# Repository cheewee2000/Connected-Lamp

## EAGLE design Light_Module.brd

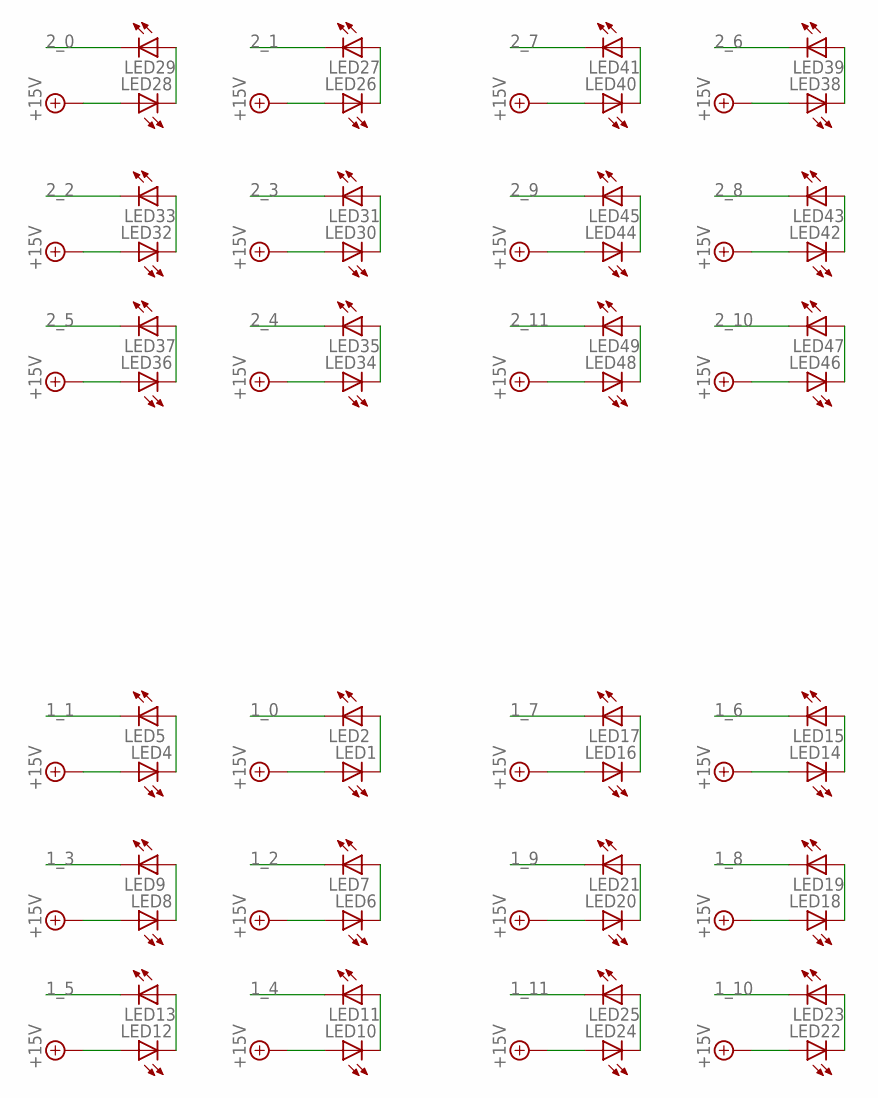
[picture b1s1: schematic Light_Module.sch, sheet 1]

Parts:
LED1, LED2, LED4, LED5, LED6, LED7, LED8, LED9, LED10, LED11, LED12, LED13, LED14, LED15, LED16, LED17, LED18, LED19, LED20, LED21, LED22, LED23, LED24, LED25, LED26, LED27, LED28, LED29, LED30, LED31, LED32, LED33, LED34, LED35, LED36, LED37, LED38, LED39, LED40, LED41, LED42, LED43, LED44, LED45, LED46, LED47, LED48, LED49: LED; DS205

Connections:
1_0: LED2.P$2 (C); also elsewhere on the board
1_1: LED5.P$2 (C); also elsewhere on the board
1_2: LED7.P$2 (C); also elsewhere on the board
1_3: LED9.P$2 (C); also elsewhere on the board
1_4: LED11.P$2 (C); also elsewhere on the board
1_5: LED13.P$2 (C); also elsewhere on the board
1_6: LED15.P$2 (C); also elsewhere on the board
1_7: LED17.P$2 (C); also elsewhere on the board
1_8: LED19.P$2 (C); also elsewhere on the board
1_9: LED21.P$2 (C); also elsewhere on the board
1_10: LED23.P$2 (C); also elsewhere on the board
1_11: LED25.P$2 (C); also elsewhere on the board
2_0: LED29.P$2 (C); also elsewhere on the board
2_1: LED27.P$2 (C); also elsewhere on the board
2_2: LED33.P$2 (C); also elsewhere on the board
2_3: LED31.P$2 (C); also elsewhere on the board
2_4: LED35.P$2 (C); also elsewhere on the board
2_5: LED37.P$2 (C); also elsewhere on the board
2_6: LED39.P$2 (C); also elsewhere on the board
2_7: LED41.P$2 (C); also elsewhere on the board
2_8: LED43.P$2 (C); also elsewhere on the board
2_9: LED45.P$2 (C); also elsewhere on the board
2_10: LED47.P$2 (C); also elsewhere on the board
2_11: LED49.P$2 (C); also elsewhere on the board
+15V: LED1.P$1 (A), LED4.P$1 (A), LED6.P$1 (A), LED8.P$1 (A), LED10.P$1 (A), LED12.P$1 (A), LED14.P$1 (A), LED16.P$1 (A), LED18.P$1 (A), LED20.P$1 (A), LED22.P$1 (A), LED24.P$1 (A), LED26.P$1 (A), LED28.P$1 (A), LED30.P$1 (A), LED32.P$1 (A), LED34.P$1 (A), LED36.P$1 (A), LED38.P$1 (A), LED40.P$1 (A), LED42.P$1 (A), LED44.P$1 (A), LED46.P$1 (A), LED48.P$1 (A); also elsewhere on the board
unnamed: LED1.P$2 (C), LED2.P$1 (A)
unnamed: LED4.P$2 (C), LED5.P$1 (A)
unnamed: LED6.P$2 (C), LED7.P$1 (A)
unnamed: LED8.P$2 (C), LED9.P$1 (A)
unnamed: LED10.P$2 (C), LED11.P$1 (A)
unnamed: LED12.P$2 (C), LED13.P$1 (A)
unnamed: LED14.P$2 (C), LED15.P$1 (A)
unnamed: LED16.P$2 (C), LED17.P$1 (A)
unnamed: LED18.P$2 (C), LED19.P$1 (A)
unnamed: LED20.P$2 (C), LED21.P$1 (A)
unnamed: LED22.P$2 (C), LED23.P$1 (A)
unnamed: LED24.P$2 (C), LED25.P$1 (A)
unnamed: LED26.P$2 (C), LED27.P$1 (A)
unnamed: LED28.P$2 (C), LED29.P$1 (A)
unnamed: LED30.P$2 (C), LED31.P$1 (A)
unnamed: LED32.P$2 (C), LED33.P$1 (A)
unnamed: LED34.P$2 (C), LED35.P$1 (A)
unnamed: LED36.P$2 (C), LED37.P$1 (A)
unnamed: LED38.P$2 (C), LED39.P$1 (A)
unnamed: LED40.P$2 (C), LED41.P$1 (A)
unnamed: LED42.P$2 (C), LED43.P$1 (A)
unnamed: LED44.P$2 (C), LED45.P$1 (A)
unnamed: LED46.P$2 (C), LED47.P$1 (A)
unnamed: LED48.P$2 (C), LED49.P$1 (A)

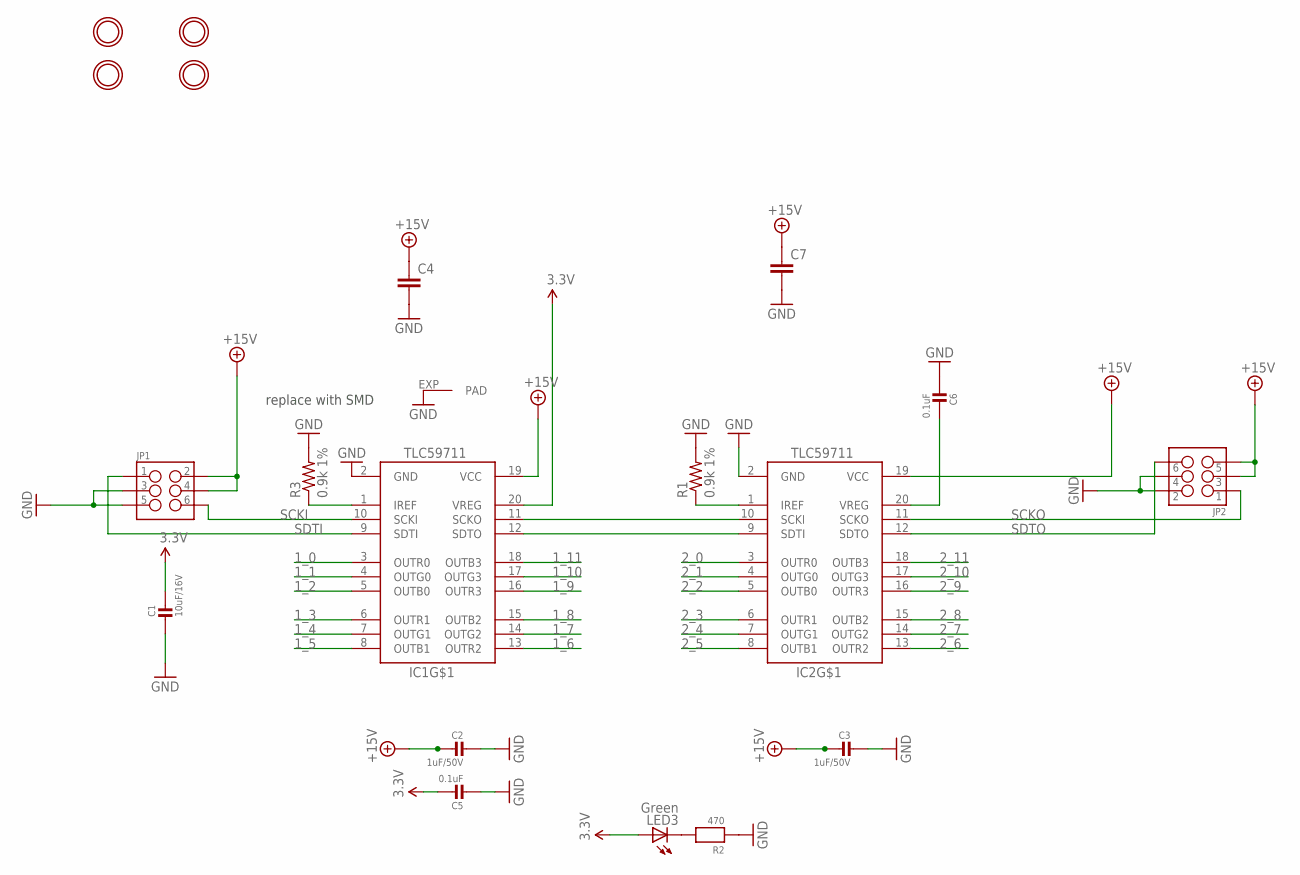
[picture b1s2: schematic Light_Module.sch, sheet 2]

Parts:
C1: 10uF/16V; 0805
C2, C3: 1uF/50V; 0805
C4: CAP1206; 1206
C5, C6: 0.1uF; 0805
C7: CAP_; AXIAL-5MM
IC1, IC2: TLC59711; HTSSOP20DAP
JP1, JP2: M03X2FEMALE_SMD; 2X3_SMD
LED3: Green; CHIP-LED0805
R1, R3: 0.9k 1%; 1206
R2: 470; 0805
U$1, U$2, U$3, U$4: MOUNTINGHOLE2.5; MOUNTINGHOLE_2.5_PLATED

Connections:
1_0: IC1.3 (OUTR0); also elsewhere on the board
1_1: IC1.4 (OUTG0); also elsewhere on the board
1_2: IC1.5 (OUTB0); also elsewhere on the board
1_3: IC1.6 (OUTR1); also elsewhere on the board
1_4: IC1.7 (OUTG1); also elsewhere on the board
1_5: IC1.8 (OUTB1); also elsewhere on the board
1_6: IC1.13 (OUTR2); also elsewhere on the board
1_7: IC1.14 (OUTG2); also elsewhere on the board
1_8: IC1.15 (OUTB2); also elsewhere on the board
1_9: IC1.16 (OUTR3); also elsewhere on the board
1_10: IC1.17 (OUTG3); also elsewhere on the board
1_11: IC1.18 (OUTB3); also elsewhere on the board
2_0: IC2.3 (OUTR0); also elsewhere on the board
2_1: IC2.4 (OUTG0); also elsewhere on the board
2_2: IC2.5 (OUTB0); also elsewhere on the board
2_3: IC2.6 (OUTR1); also elsewhere on the board
2_4: IC2.7 (OUTG1); also elsewhere on the board
2_5: IC2.8 (OUTB1); also elsewhere on the board
2_6: IC2.13 (OUTR2); also elsewhere on the board
2_7: IC2.14 (OUTG2); also elsewhere on the board
2_8: IC2.15 (OUTB2); also elsewhere on the board
2_9: IC2.16 (OUTR3); also elsewhere on the board
2_10: IC2.17 (OUTG3); also elsewhere on the board
2_11: IC2.18 (OUTB3); also elsewhere on the board
3.3V: C1.1, C5.1, IC1.20 (VREG), LED3.A
+15V: C2.1, C3.1, C4.1, C7.P$1 (1), IC1.19 (VCC), IC2.19 (VCC), JP1.2, JP1.4, JP2.3, JP2.5; also elsewhere on the board
GND: C1.2, C2.2, C3.2, C4.2, C5.2, C6.2, C7.P$2 (2), IC1.2 (GND), IC1.EXP (PAD), IC2.2 (GND), JP1.3, JP1.5, JP2.2, JP2.4, R1.2, R2.1, R3.2
unnamed: LED3.C, R2.2
unnamed: IC1.1 (IREF), R3.1
unnamed: IC2.1 (IREF), R1.1
unnamed: IC1.11 (SCKO), IC2.10 (SCKI)
unnamed: IC1.12 (SDTO), IC2.9 (SDTI)
unnamed: C6.1, IC2.20 (VREG)
SCKI: IC1.10 (SCKI), JP1.6
SCKO: IC2.11 (SCKO), JP2.1
SDTI: IC1.9 (SDTI), JP1.1
SDTO: IC2.12 (SDTO), JP2.6

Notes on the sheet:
replace with SMD

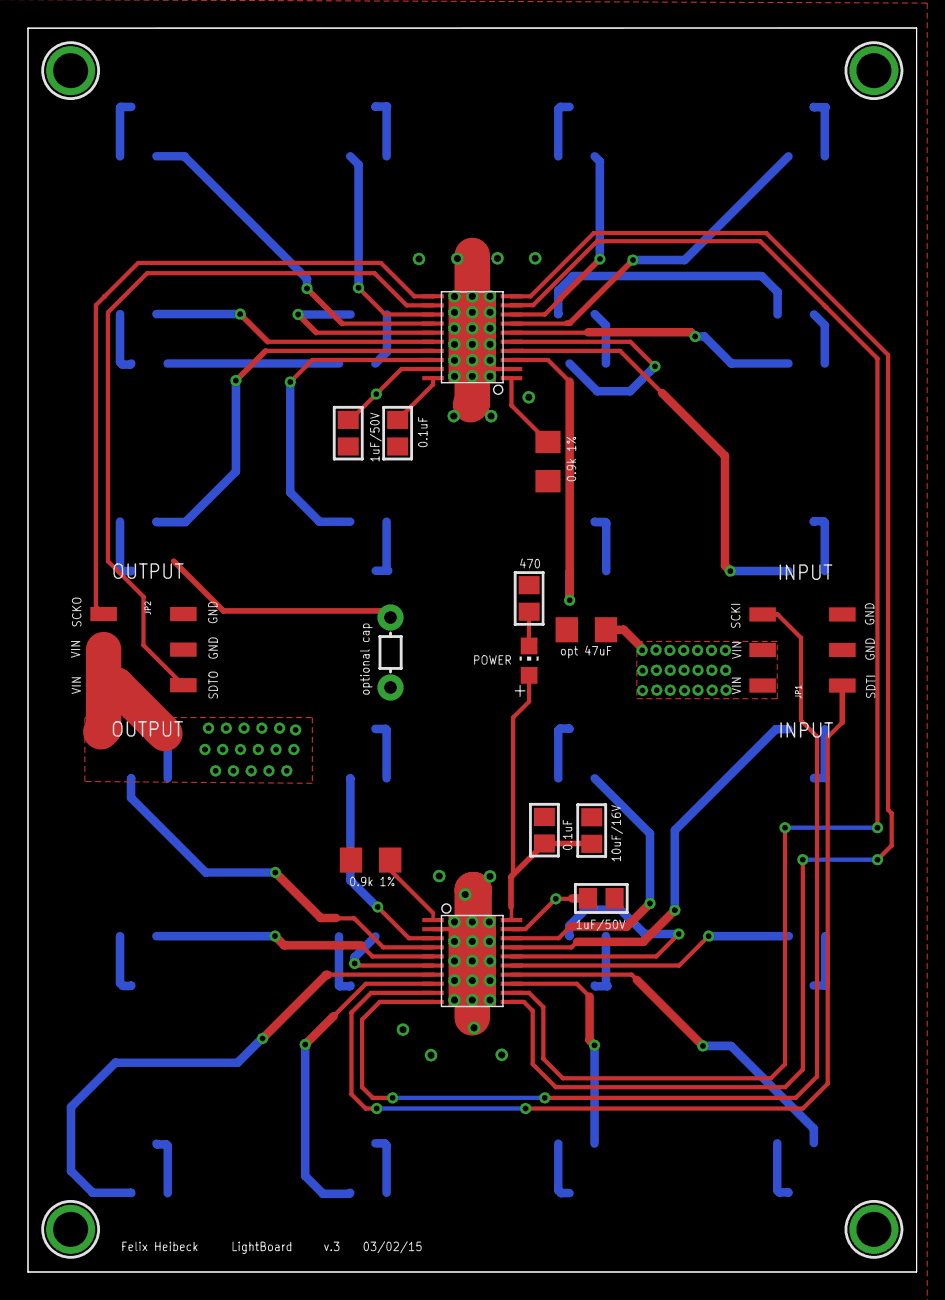
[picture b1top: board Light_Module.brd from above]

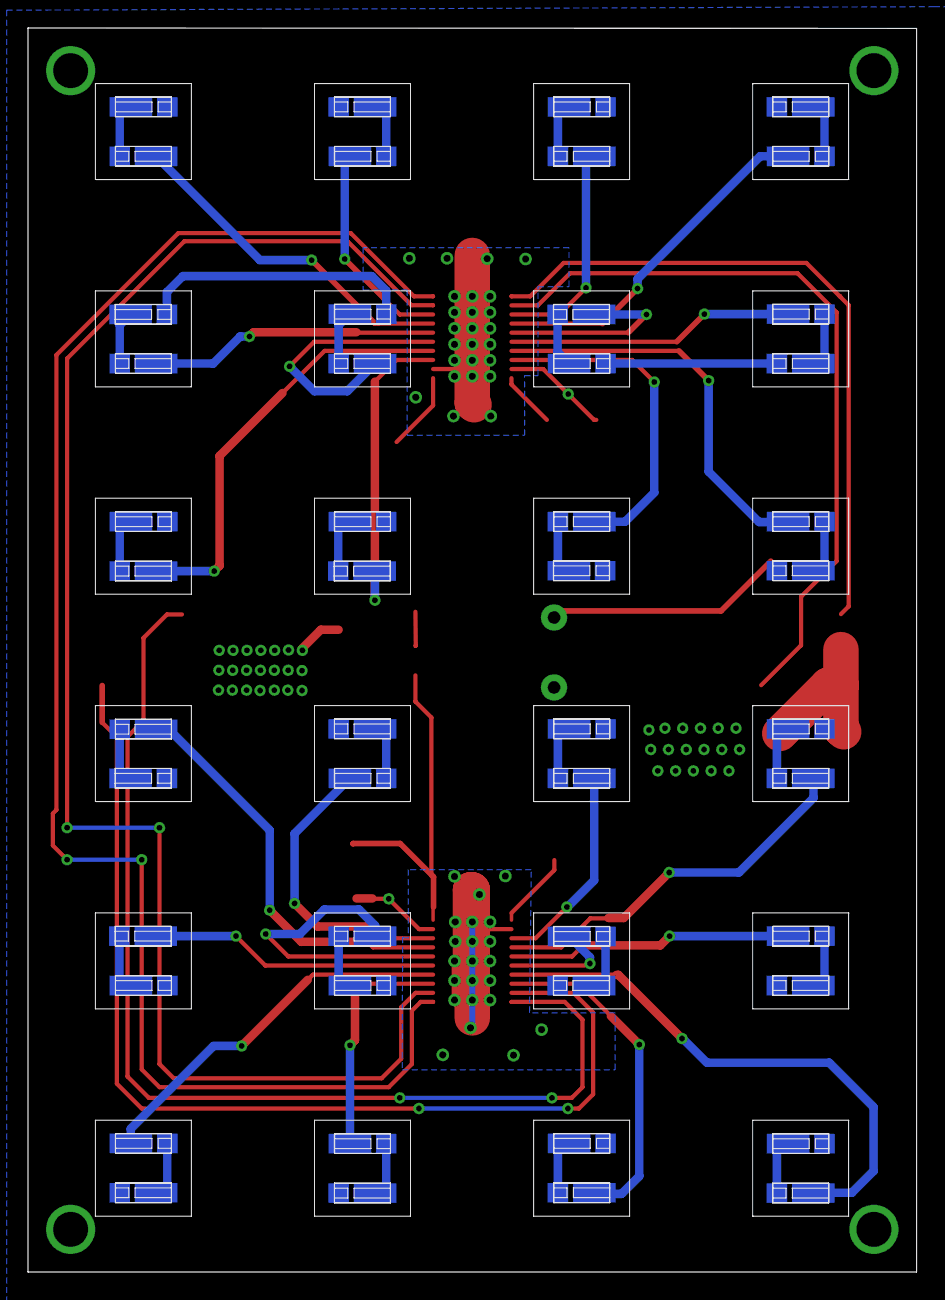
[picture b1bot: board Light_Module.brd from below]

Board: 2 copper layers, 63.5 x 88.9 mm, 67 parts (48 on the bottom side), 61 nets.

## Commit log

2015-02-18 create
2015-03-12 small revision
    delete v.1 - fix small missing connection
2015-05-10 Revert 42a1a8e..717766d
    This rolls back to commit 42a1a8ecaa921d949cbaf7c99d83dff5afafc410.

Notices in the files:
parts and their libraries:
microbuilder: This work is placed in the public domain, and may be freely used for commercial and non-commercial work with the following conditions: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
SparkFun-Passives: Licensing: Creative Commons ShareAlike 4.0 International - https://creativecommons.org/licenses/by-sa/4.0
